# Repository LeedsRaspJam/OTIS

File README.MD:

# OTIS
 * This repository is used to host a Pages site, see [otis.leedsraspjam.co.uk](https://otis.leedsraspjam.co.uk) for the finished docs.

* Built using [reStructuredText](https://www.sphinx-doc.org/en/master/usage/restructuredtext/basics.html) and [Sphinx](https://www.sphinx-doc.org/en/master/). Make sure to move the successfull build files from sphinx-dir/build/html to root before committing.
# Useful Files
 * [LICENSE.MD](LICENSE.MD) - Contains licensing info for this repo
 * [/docs](docs) - Contains the built html files
# Building Locally
1) First make sure you have ```sphinx```, ```sphinx-rtd-theme``` and ```sphinxembeddedvideos``` installed. If you haven't installed these you can run ```pip3 install [PACKAGE_NAME]```
2) Next navigate to the [sphinx-dir](sphinx-dir) and run ```make html```. This will build the site and put the outputted HTML files in ```build/html```
3) You can then move the HTML files to the root of your web server
# Editing the files
 * All the source is located in [sphinx-dir/source](sphinx-dir/source), the index file is [sphinx-dir/source/index.rst](sphinx-dir/source/index.rst) and each step is labeled ```s[STEPNUM].rst```.
 * The project name, copyright info and author can be changed in [sphinx-dir/source/conf.py](sphinx-dir/source/conf.py) along with any new extensions that are needed.

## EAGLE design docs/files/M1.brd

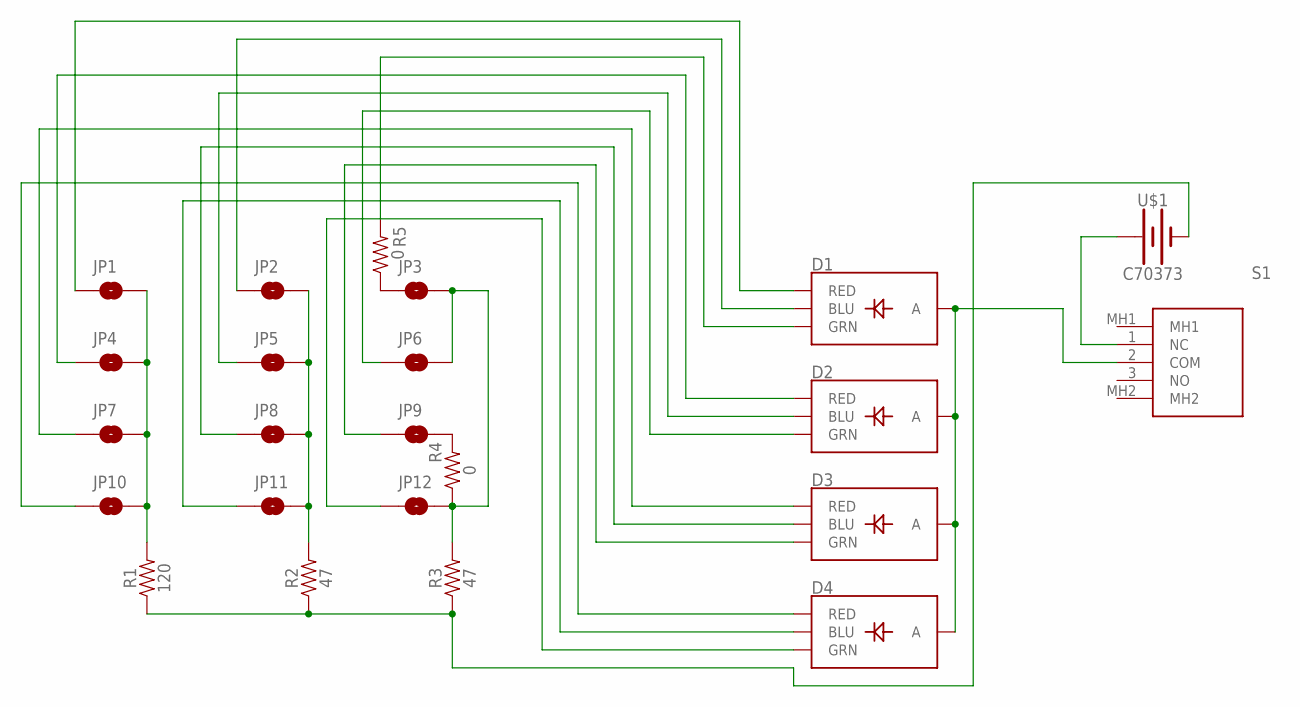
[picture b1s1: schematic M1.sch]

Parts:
D1, D2, D3, D4: LED-RGB-CACLEAR; LED-RGB-THRU
JP1, JP2, JP3, JP4, JP5, JP6, JP7, JP8, JP9, JP10, JP11, JP12: JUMPER-SMT_2_NO_SILK; SMT-JUMPER_2_NO_SILK
R1: 120; 0805
R2, R3: 47; 0805
R4, R5: 0; 0805
S1: SK12D07VG4
U$1: C70373; CR2032

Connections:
unnamed: D1.2 (A), D2.2 (A), D3.2 (A), D4.2 (A), S1.2 (COM)
unnamed: S1.1 (NC), U$1.P$2 (+)
unnamed: D1.1 (RED), JP1.1
unnamed: JP3.2, JP6.2, JP12.2, R3.2, R4.1
unnamed: D1.4 (BLU), JP2.1
unnamed: D1.3 (GRN), R5.2
unnamed: D2.4 (BLU), JP5.1
unnamed: D3.4 (BLU), JP8.1
unnamed: D2.3 (GRN), JP6.1
unnamed: D4.4 (BLU), JP11.1
unnamed: D3.3 (GRN), JP9.1
unnamed: D4.3 (GRN), JP12.1
unnamed: D2.1 (RED), JP4.1
unnamed: D3.1 (RED), JP7.1
unnamed: D4.1 (RED), JP10.1
unnamed: JP1.2, JP4.2, JP7.2, JP10.2, R1.2
unnamed: JP9.2, R4.2
unnamed: JP3.1, R5.1
unnamed: JP2.2, JP5.2, JP8.2, JP11.2, R2.2
unnamed: R1.1, R2.1, R3.1, U$1.P$1 (-)

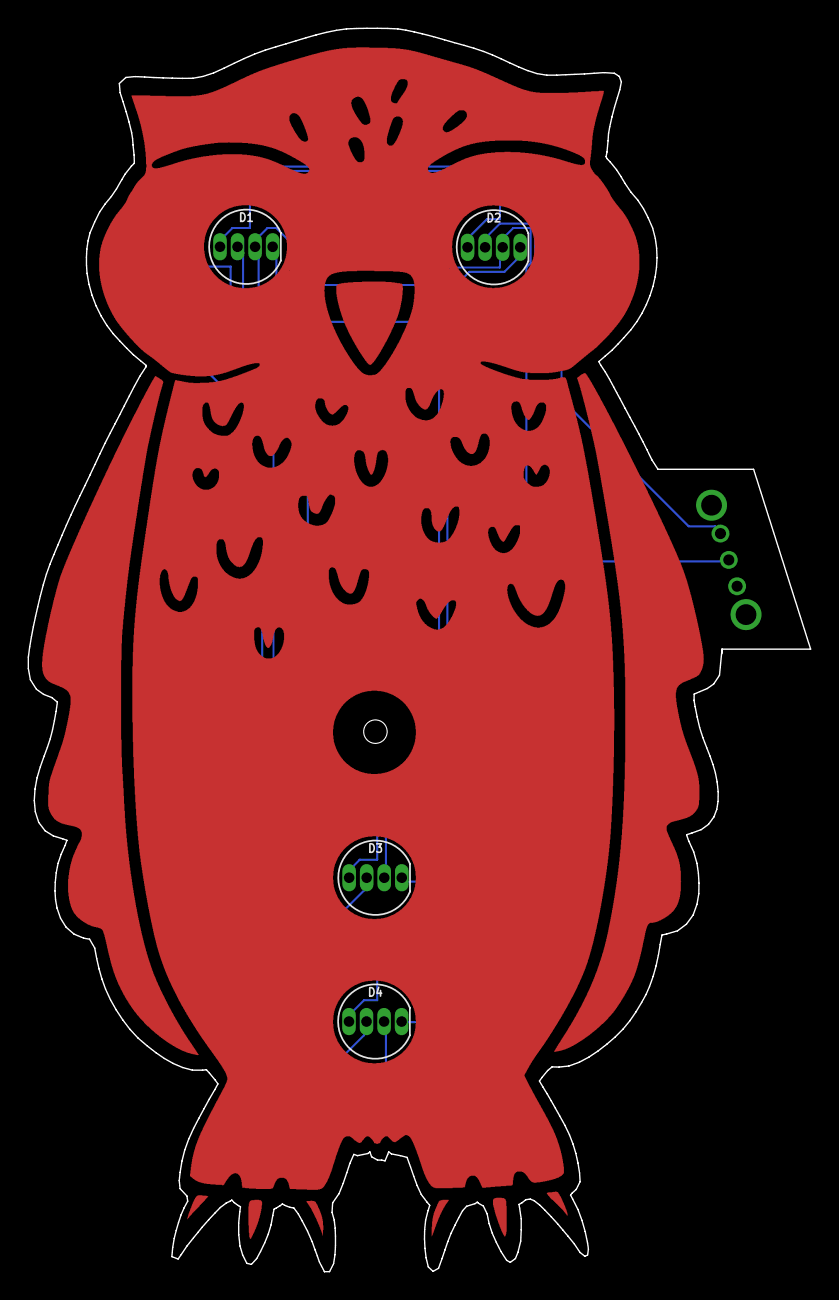
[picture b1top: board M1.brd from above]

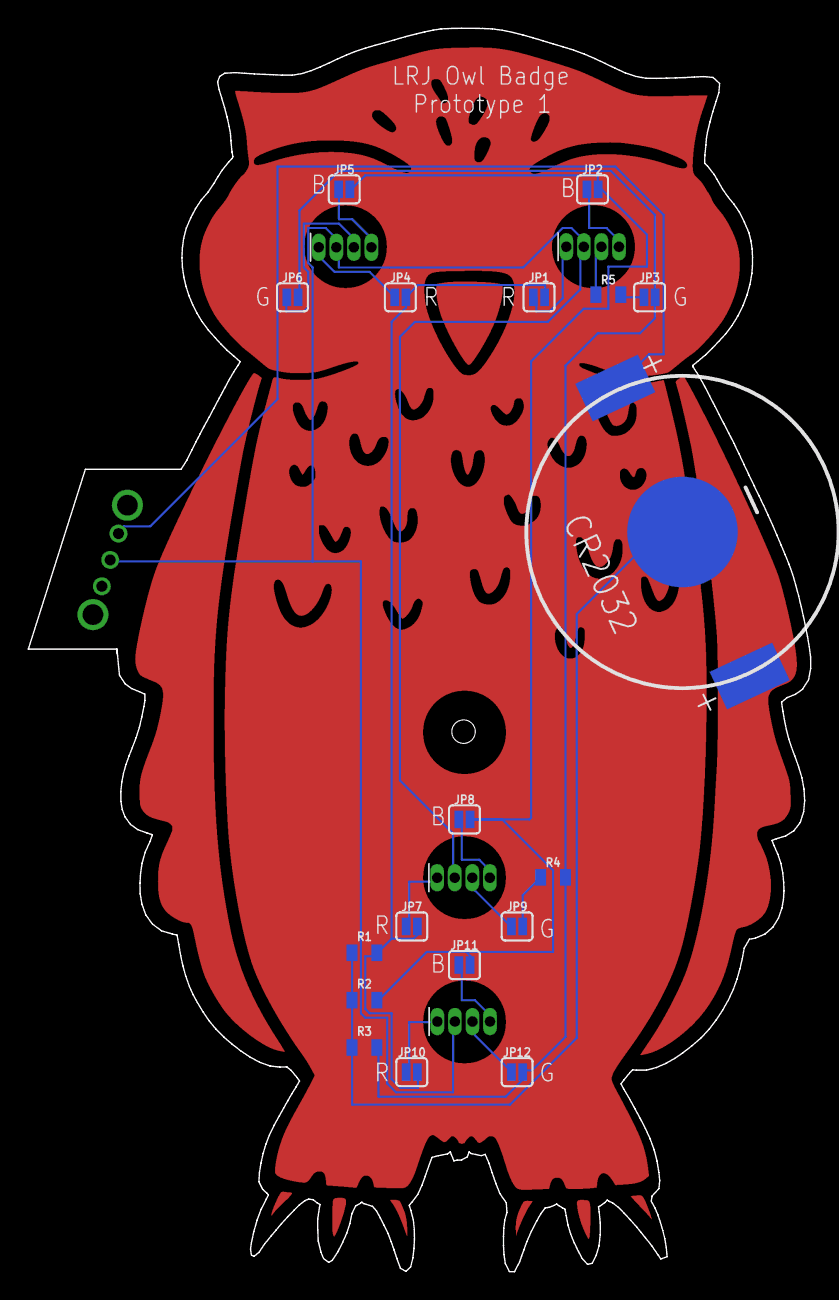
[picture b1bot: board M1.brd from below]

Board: 2 copper layers, 56.6 x 90.0 mm, 23 parts (18 on the bottom side), 20 nets.

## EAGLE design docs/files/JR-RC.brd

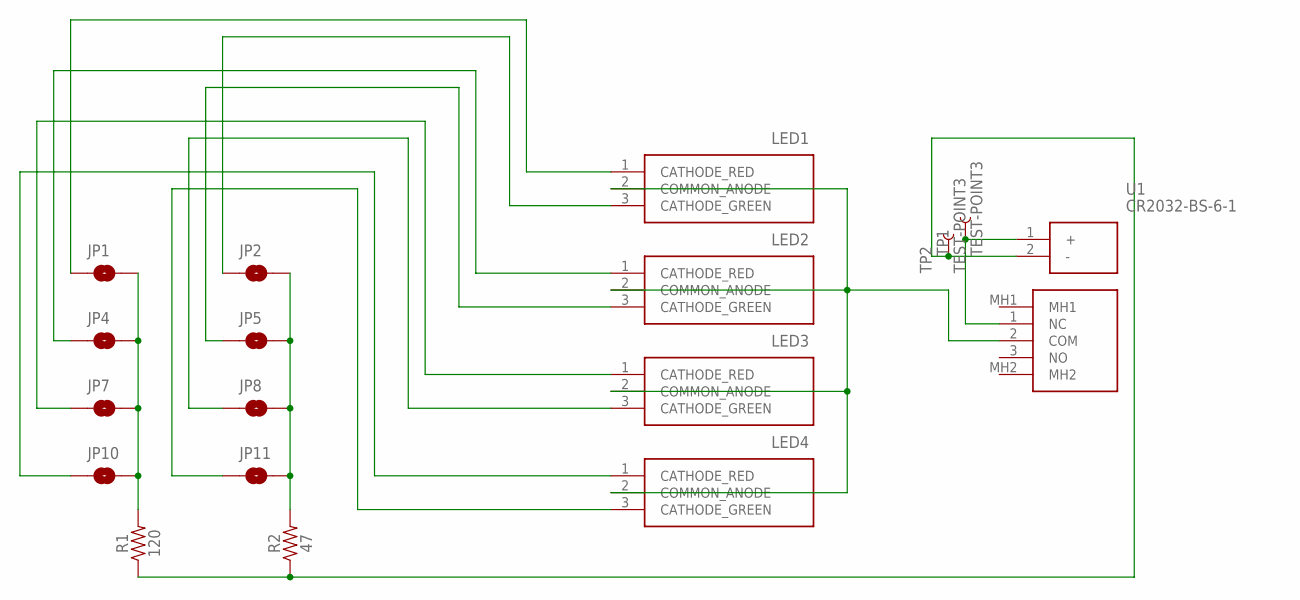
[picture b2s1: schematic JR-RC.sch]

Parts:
JP1, JP2, JP4, JP5, JP7, JP8, JP10, JP11: JUMPER-SMT_2_NO_SILK; SMT-JUMPER_2_NO_SILK
LED1, LED2, LED3, LED4: TJ-L5FYTXHMCYLC2R7K-A5
R1: 120; 1206
R2: 47; 1206
S1: SK12D07VG4
TP1, TP2: TEST-POINT3; PAD.03X.03
U1: CR2032-BS-6-1; CR2032BS61

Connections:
unnamed: LED1.2 (COMMON_ANODE), LED2.2 (COMMON_ANODE), LED3.2 (COMMON_ANODE), LED4.2 (COMMON_ANODE), S1.2 (COM)
unnamed: S1.1 (NC), TP1.P$1, U1.1 (+)
unnamed: JP1.1, LED1.1 (CATHODE_RED)
unnamed: JP2.1, LED1.3 (CATHODE_GREEN)
unnamed: JP5.1, LED2.3 (CATHODE_GREEN)
unnamed: JP8.1, LED3.3 (CATHODE_GREEN)
unnamed: JP11.1, LED4.3 (CATHODE_GREEN)
unnamed: JP4.1, LED2.1 (CATHODE_RED)
unnamed: JP7.1, LED3.1 (CATHODE_RED)
unnamed: JP10.1, LED4.1 (CATHODE_RED)
unnamed: JP1.2, JP4.2, JP7.2, JP10.2, R1.2
unnamed: R1.1, R2.1, TP2.P$1, U1.2 (-)
unnamed: JP2.2, JP5.2, JP8.2, JP11.2, R2.2

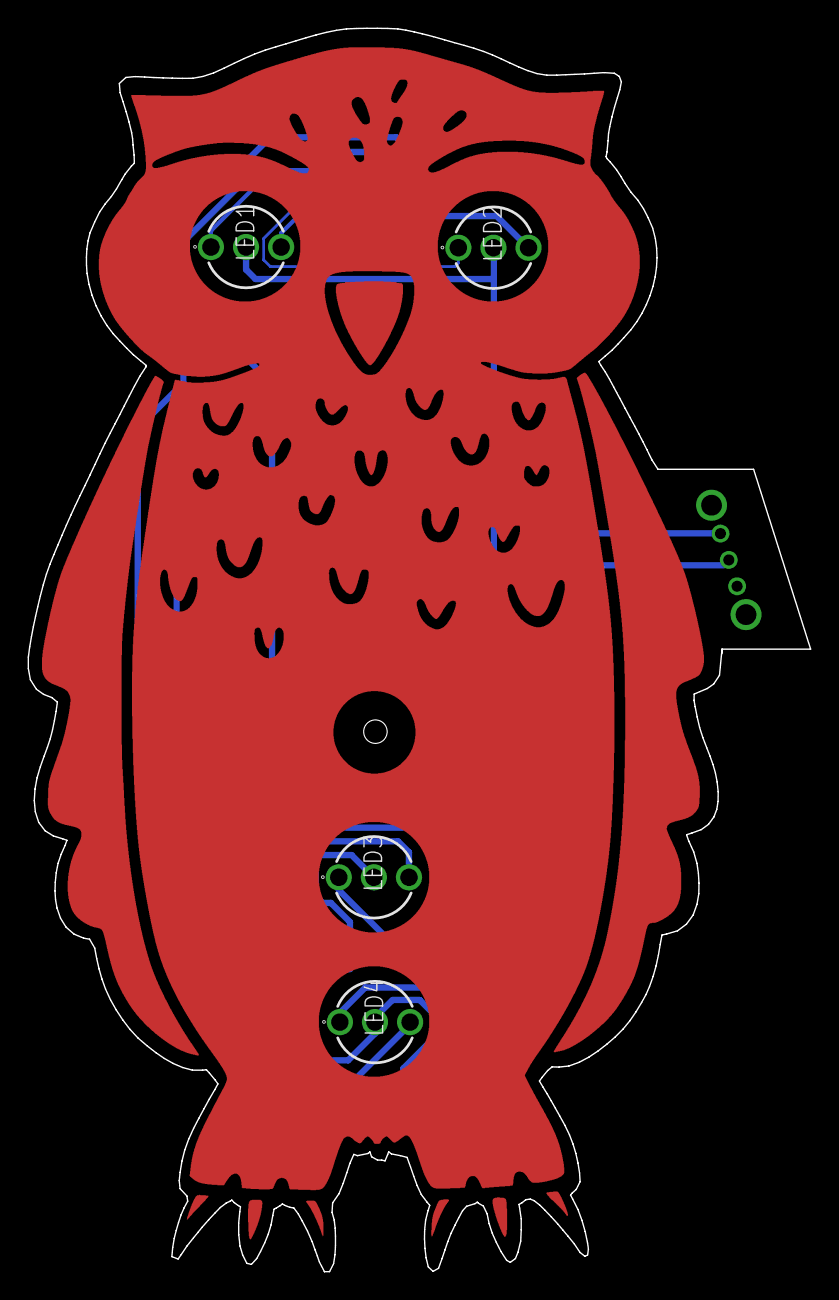
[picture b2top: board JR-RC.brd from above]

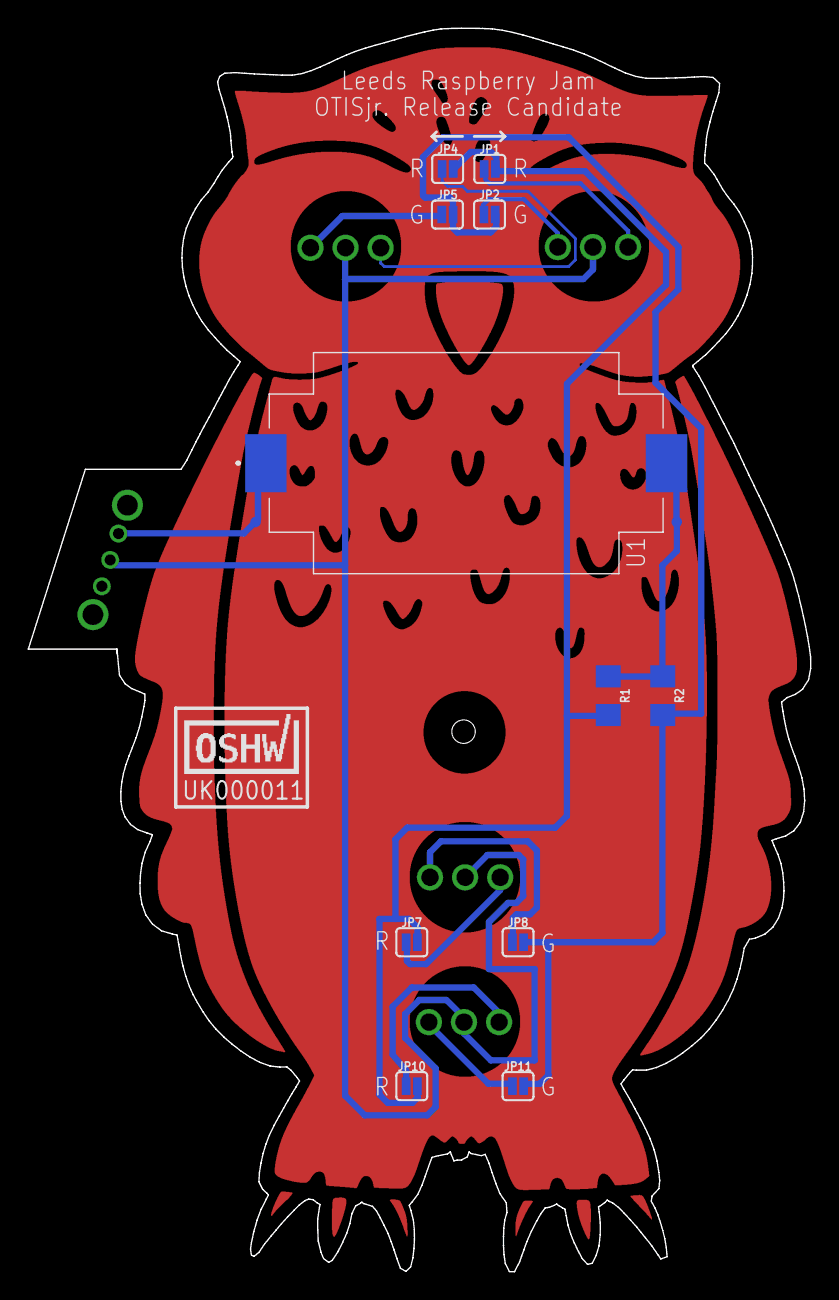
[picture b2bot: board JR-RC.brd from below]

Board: 2 copper layers, 56.6 x 90.0 mm, 19 parts (14 on the bottom side), 13 nets.

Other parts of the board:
U$1: UK000011; CERT-SMALL-SILK

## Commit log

2020-03-29 Move to root
2020-03-29 Create CNAME
2020-03-29 Update CNAME
2020-03-29 Add to the homepage + credits
2020-04-08 Fix battery text
2020-05-15 Add files + update website
2020-05-15 Add image to step 6
2020-06-05 Add statcounter code
2020-06-06 Add unsoldered resistor info
2020-06-06 Update various things on the site
2020-06-06 Fix an error
2020-06-06 Fix yet another error
2020-06-08 Add link to feedback form
2020-06-12 Change to OSHWA compliant license,
2020-06-21 Change web address
2020-06-21 Fixed various things
2020-06-21 Fix the fixes
2020-06-21 Remove statcounter
2020-06-24 Add gitignore
2020-06-24 Add videos
2020-06-24 Add video and update fommatting
2020-06-25 Begin process of porting the side to Sphinx
2020-06-25 Remove that for now
2020-06-28 New webiste + archive old one
2020-06-28 Move html files
2020-06-28 Remove old
2020-06-28 Add it back
2020-06-28 And delete it again
2020-06-28 Add archive warning
2020-06-29 Add info
2020-06-29 Add useful files
2020-06-29 Make output clearer
2020-07-02 Add oshwa mark
2020-07-02 Add colour picker (BETA!)
2020-07-02 Move html
2020-07-02 Fix scaling on overlays
2020-07-02 Add warning
2020-07-02 Fix url
2020-07-02 Fix it... again
2020-07-04 Add node folders
2020-07-04 Update colour picker
2020-07-04 Remove notice
2020-07-04 Remove debugging outputs and add comments
2020-07-04 Update files to RC
2020-07-04 Remove redundant links + update CERN link
2020-07-05 Fix comment in js
2020-07-05 Add jr. colour picker
2020-07-06 Remove readme link
2020-07-07 Move to docs folder
2020-07-07 Move files
2020-07-07 Remove node
2020-07-07 Add no jekyll
2020-07-07 Add docs folder link
2020-07-15 Test commit
2020-07-15 Create test
2020-07-15 Add tindie link and change link
2020-07-16 Fix typo
2020-07-16 Move favicon
2020-07-17 Move in new site
2020-07-17 Delete CNAME
    No longer needed as its in the docs folder now
2020-07-17 Remove troubleshooting info
    No longer needed
2020-07-17 Add final files
2020-07-17 Add jr. eagle files
2020-07-17 Add bom
2020-07-18 Add soldering tutorial
2020-07-19 Fix grammar
2020-07-20 Add 404
2020-07-20 Fix 404?
2020-07-20 Add images
2020-07-20 Move
2020-07-22 Add youtube video
2020-07-22 Put files into docs folder
2020-07-22 Revert "Add youtube video"
2020-07-22 Add new youtube videos
2020-07-22 Change width of video and disable autoplay
2020-07-22 Add video
2020-07-22 Add videos v859498
2020-07-26 Update video
2020-07-26 Build
2020-07-26 Fix yt embed code
2020-08-04 Add tindie link
2020-08-12 Vscode stuff
2020-08-12 Update index video
2020-08-12 Copy build to docs folder
2020-08-12 Fix warnings
2020-08-14 Fix shipping issue
2020-08-23 Update store links
2020-11-24 Final commit

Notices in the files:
parts and their libraries:
SparkFun-Jumpers: Licensing: Creative Commons ShareAlike 4.0 International - https://creativecommons.org/licenses/by-sa/4.0
